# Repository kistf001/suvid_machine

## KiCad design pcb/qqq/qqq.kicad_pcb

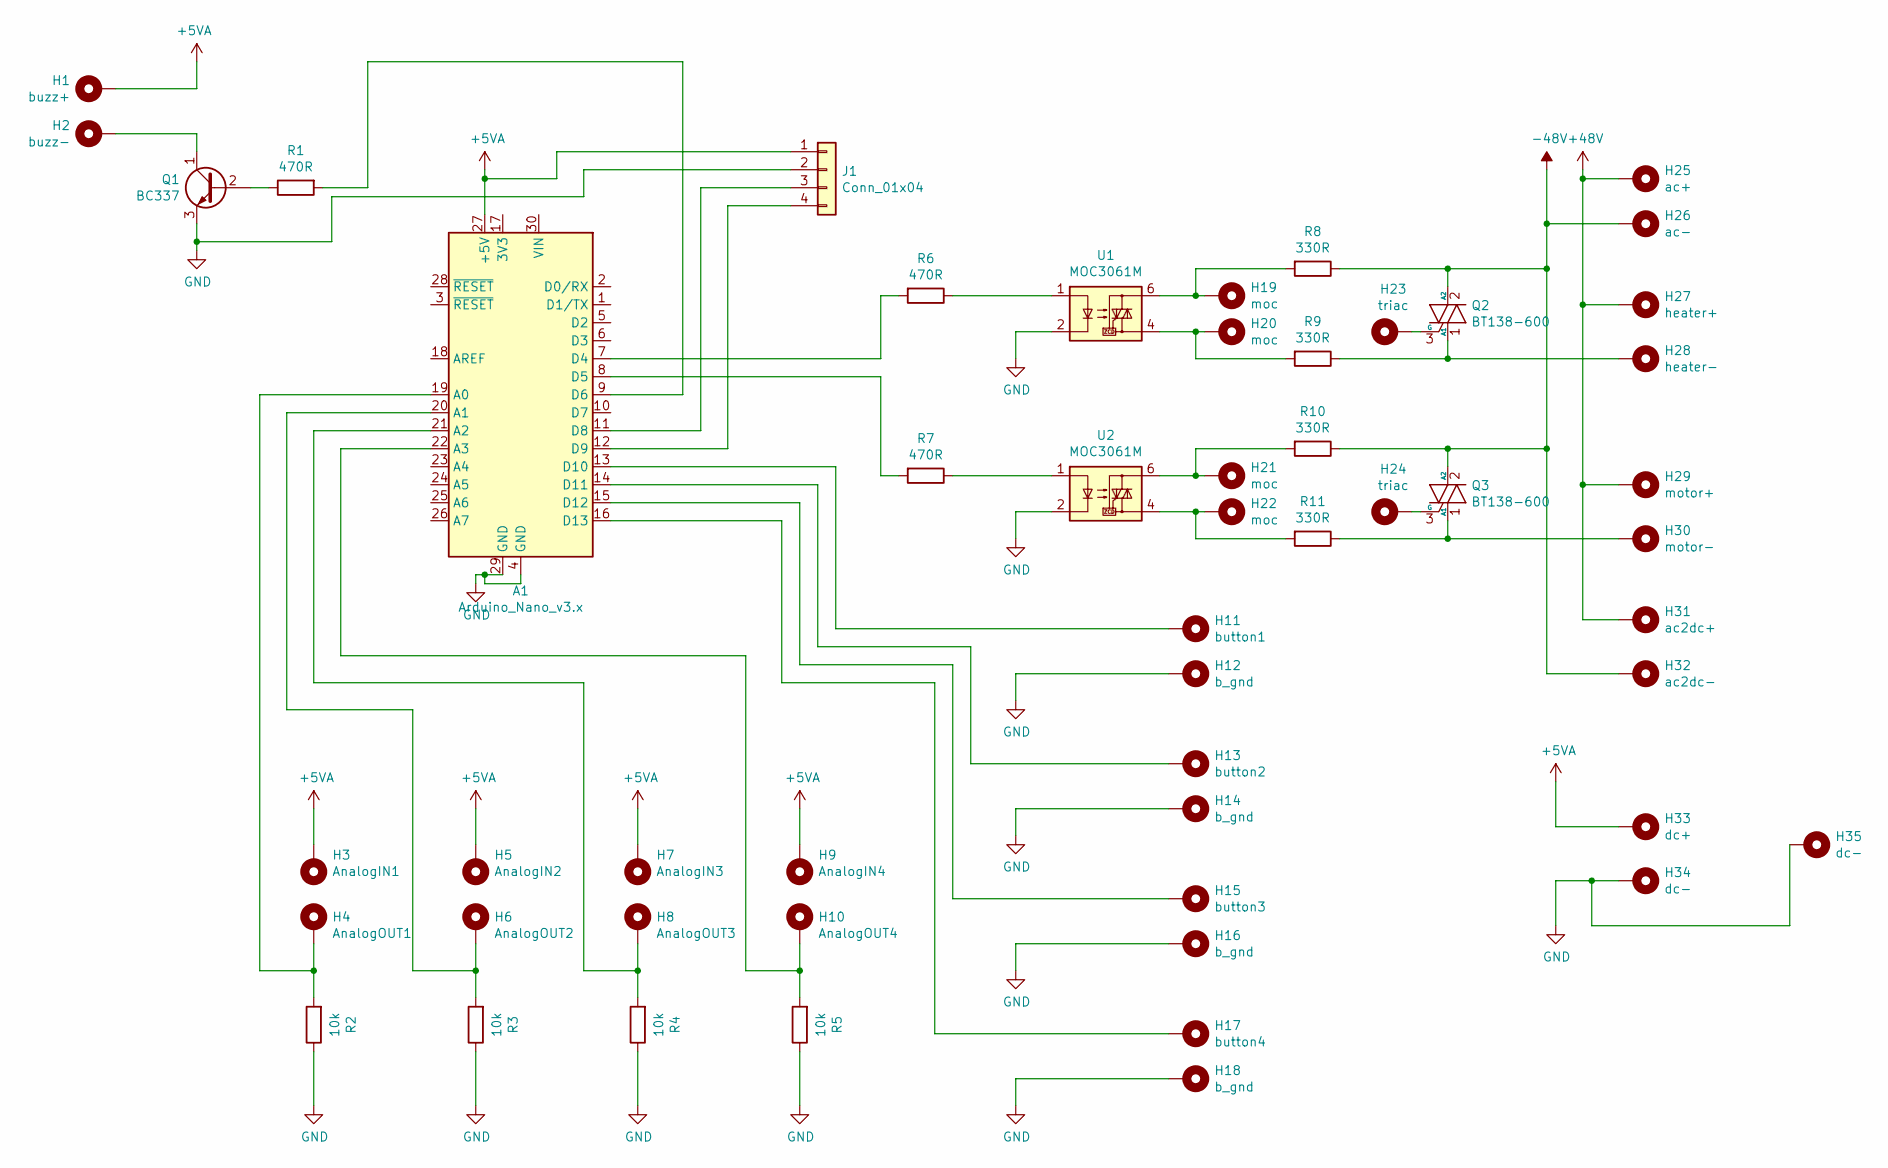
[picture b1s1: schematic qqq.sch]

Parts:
A1: Arduino_Nano_v3.x; Arduino_Nano
H1: buzz+; PinHeader_1x01_P2.54mm_Vertical
H2: buzz-; PinHeader_1x01_P2.54mm_Vertical
H3: AnalogIN1; PinHeader_1x01_P2.54mm_Vertical
H4: AnalogOUT1; PinHeader_1x01_P2.54mm_Vertical
H5: AnalogIN2; PinHeader_1x01_P2.54mm_Vertical
H6: AnalogOUT2; PinHeader_1x01_P2.54mm_Vertical
H7: AnalogIN3; PinHeader_1x01_P2.54mm_Vertical
H8: AnalogOUT3; PinHeader_1x01_P2.54mm_Vertical
H9: AnalogIN4; PinHeader_1x01_P2.54mm_Vertical
H10: AnalogOUT4; PinHeader_1x01_P2.54mm_Vertical
H11: button1; PinHeader_1x01_P2.54mm_Vertical
H12, H14, H16, H18: b_gnd; PinHeader_1x01_P2.54mm_Vertical
H13: button2; PinHeader_1x01_P2.54mm_Vertical
H15: button3; PinHeader_1x01_P2.54mm_Vertical
H17: button4; PinHeader_1x01_P2.54mm_Vertical
H19, H20, H21, H22: moc; PinHeader_1x01_P2.54mm_Vertical
H23, H24: triac; PinHeader_1x01_P2.54mm_Vertical
H25: ac+; MountingHole_2.7mm_M2.5_ISO7380_Pad
H26: ac-; MountingHole_2.7mm_M2.5_ISO7380_Pad
H27: heater+; MountingHole_2.7mm_M2.5_ISO7380_Pad
H28: heater-; MountingHole_2.7mm_M2.5_ISO7380_Pad
H29: motor+; MountingHole_2.7mm_M2.5_ISO7380_Pad
H30: motor-; MountingHole_2.7mm_M2.5_ISO7380_Pad
H31: ac2dc+; PinHeader_1x01_P2.54mm_Vertical
H32: ac2dc-; PinHeader_1x01_P2.54mm_Vertical
H33: dc+; PinHeader_1x01_P2.54mm_Vertical
H34: dc-; PinHeader_1x01_P2.54mm_Vertical
H35: dc-; MountingHole_2.2mm_M2_Pad
J1: Conn_01x04; PinHeader_1x04_P2.54mm_Vertical
Q1: BC337; TO-92_Inline
Q2, Q3: BT138-600; TO-220-3_Vertical
R1, R6, R7: 470R; R_Axial_DIN0309_L9.0mm_D3.2mm_P5.08mm_Vertical
R2, R3, R4, R5: 10k; R_Axial_DIN0309_L9.0mm_D3.2mm_P2.54mm_Vertical
R8, R9, R10, R11: 330R; R_Axial_DIN0309_L9.0mm_D3.2mm_P5.08mm_Vertical
U1, U2: MOC3061M; DIP-6_W7.62mm

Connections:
+5VA: A1.27 (+5V), H1.1, H3.1, H5.1, H7.1, H9.1, H33.1, J1.1
+48V: H25.1, H27.1, H29.1, H31.1
-48V: H26.1, H32.1, Q2.2 (A2), Q3.2 (A2), R8.1, R10.1
GND: A1.4 (GND), A1.29 (GND), H12.1, H14.1, H16.1, H18.1, H34.1, H35.1, J1.2, Q1.3 (E), R2.1, R3.1, R4.1, R5.1, U1.2, U2.2
unnamed: A1.7 (D4), R6.2
unnamed: A1.8 (D5), R7.2
unnamed: A1.9 (D6), R1.2
unnamed: A1.11 (D8), J1.3
unnamed: A1.12 (D9), J1.4
unnamed: A1.13 (D10), H11.1
unnamed: A1.14 (D11), H13.1
unnamed: A1.15 (D12), H15.1
unnamed: A1.16 (D13), H17.1
unnamed: A1.19 (A0), H4.1, R2.2
unnamed: A1.20 (A1), H6.1, R3.2
unnamed: A1.21 (A2), H8.1, R4.2
unnamed: A1.22 (A3), H10.1, R5.2
unnamed: H2.1, Q1.1 (C)
unnamed: H19.1, R8.2, U1.6
unnamed: H20.1, R9.2, U1.4
unnamed: H21.1, R10.2, U2.6
unnamed: H22.1, R11.2, U2.4
unnamed: H23.1, Q2.3 (G)
unnamed: H24.1, Q3.3 (G)
unnamed: H28.1, Q2.1 (A1), R9.1
unnamed: H30.1, Q3.1 (A1), R11.1
unnamed: Q1.2 (B), R1.1
unnamed: R6.1, U1.1
unnamed: R7.1, U2.1

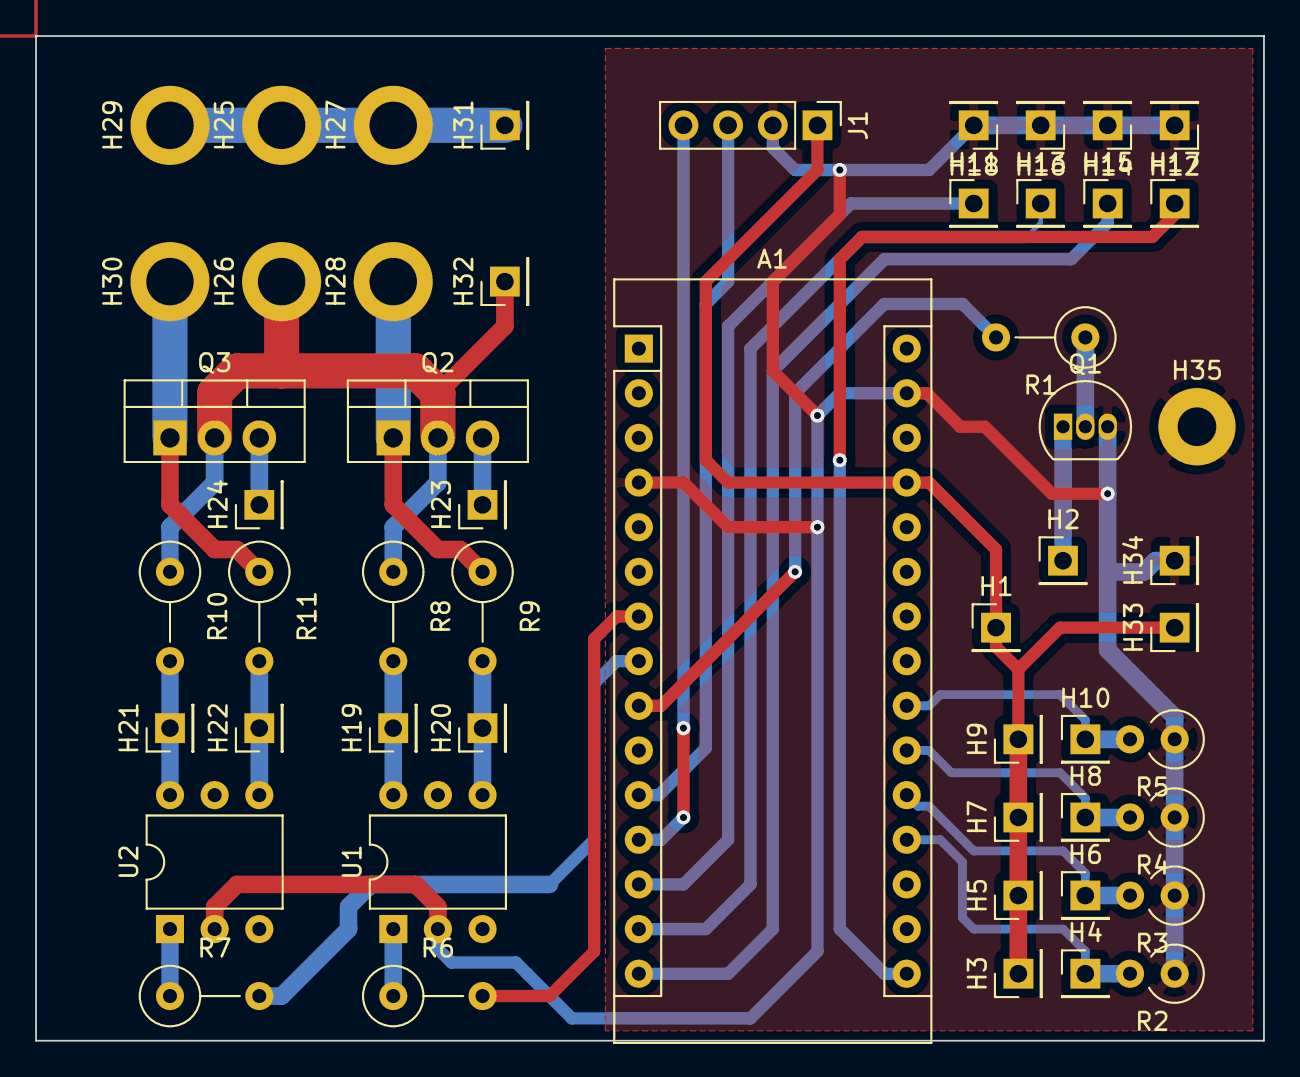
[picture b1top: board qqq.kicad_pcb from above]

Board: 2 copper layers, 69.8 x 57.1 mm, 53 parts (0 on the bottom side), 29 nets.
